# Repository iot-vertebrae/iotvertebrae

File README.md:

# IoT Vertebrae 

The vertebrae bus is an extenxion of the [UEXT](https://www.olimex.com/Products/Modules/UEXT) open bus proposed by Olimex.

This project will be provided as open-source hardware.

## [Using IoT Vertebrae](https://www-binefa-com.translate.goog/index.php/IoT-Vertebrae?_x_tr_sl=ca&_x_tr_tl=en&_x_tr_hl=es&_x_tr_pto=wapp)

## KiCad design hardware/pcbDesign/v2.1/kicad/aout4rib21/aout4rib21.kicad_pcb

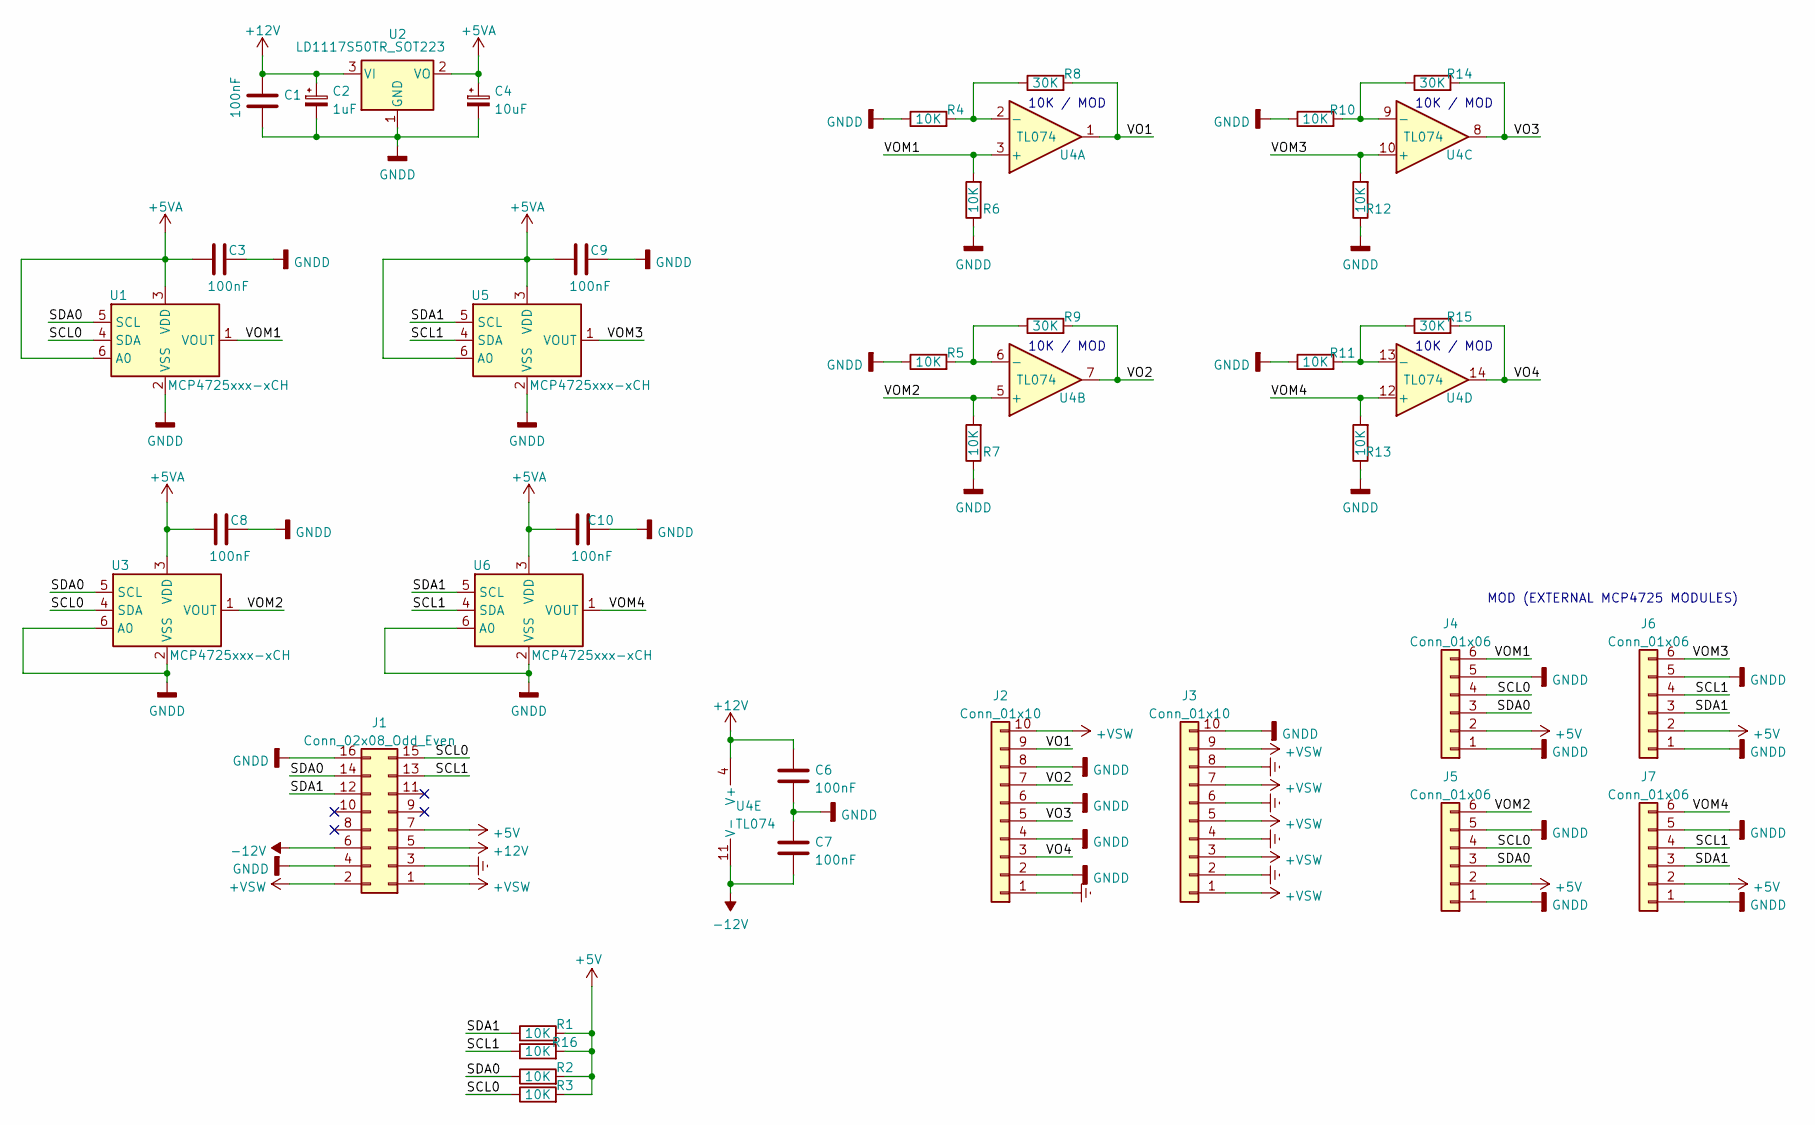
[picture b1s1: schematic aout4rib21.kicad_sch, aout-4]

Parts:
C1, C3, C6, C7, C8, C9, C10: 100nF; C_0805_2012Metric_Pad1.18x1.45mm_HandSolder
C2: 1uF; C_0805_2012Metric_Pad1.18x1.45mm_HandSolder
C4: 10uF; C_0805_2012Metric_Pad1.18x1.45mm_HandSolder
J1: Conn_02x08_Odd_Even; IDC-Header_2x08_P2.54mm_Vertical
J2: Conn_01x10; PhoenixContact_MSTBA_2,5_10-G-5,08_1x10_P5.08mm_Horizontal
J3: Conn_01x10; PhoenixContact_MSTBVA_2,5_10-G-5,08_1x10_P5.08mm_Vertical
J4, J5, J6, J7: Conn_01x06; PinSocket_1x06_P2.54mm_Vertical
R1, R2, R3, R4, R5, R6, R7, R10, R11, R12, R13, R16: 10K; R_0805_2012Metric_Pad1.20x1.40mm_HandSolder
R8, R9, R14, R15: 30K; R_0805_2012Metric_Pad1.20x1.40mm_HandSolder
U1, U3, U5, U6: MCP4725xxx-xCH; SOT-23-6
U2: LD1117S50TR_SOT223; SOT-223-3_TabPin2
U4: TL074; SOIC-14_3.9x8.7mm_P1.27mm

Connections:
+5V: J1.7, J4.2, J5.2, J6.2, J7.2, R1.2, R2.2, R3.2, R16.2
+5VA: C3.1, C4.1, C8.1, C9.1, C10.1, U1.3 (VDD), U1.6 (A0), U2.2 (VO), U3.3 (VDD), U5.3 (VDD), U5.6 (A0), U6.3 (VDD)
+12V: C1.1, C2.1, C6.1, J1.5, U2.3 (VI), U4.4 (V+)
+VSW: J1.1, J1.2, J2.10, J3.1, J3.3, J3.5, J3.7, J3.9
-12V: C7.2, J1.6, U4.11 (V-)
/SCL0: J1.15, J4.4, J5.4, R3.1, U1.4 (SDA), U3.4 (SDA)
/SCL1: J1.13, J6.4, J7.4, R16.1, U5.4 (SDA), U6.4 (SDA)
/SDA0: J1.14, J4.3, J5.3, R2.1, U1.5 (SCL), U3.5 (SCL)
/SDA1: J1.12, J6.3, J7.3, R1.1, U5.5 (SCL), U6.5 (SCL)
/VO1: J2.9, R8.2, U4.1
/VO2: J2.7, R9.2, U4.7
/VO3: J2.5, R14.2, U4.8
/VO4: J2.3, R15.2, U4.14
/VOM1: J4.6, R6.2, U1.1 (VOUT), U4.3 (+)
/VOM2: J5.6, R7.2, U3.1 (VOUT), U4.5 (+)
/VOM3: J6.6, R12.2, U4.10 (+), U5.1 (VOUT)
/VOM4: J7.6, R13.2, U4.12 (+), U6.1 (VOUT)
Earth: J1.3, J2.1, J3.2, J3.4, J3.6, J3.8
GNDD: C1.2, C2.2, C3.2, C4.2, C6.2, C7.1, C8.2, C9.2, C10.2, J1.4, J1.16, J2.2, J2.4, J2.6, J2.8, J3.10, J4.1, J4.5, J5.1, J5.5, J6.1, J6.5, J7.1, J7.5, R4.1, R5.1, R6.1, R7.1, R10.1, R11.1, R12.1, R13.1, U1.2 (VSS), U2.1 (GND), U3.2 (VSS), U3.6 (A0), U5.2 (VSS), U6.2 (VSS), U6.6 (A0)
unnamed: R4.2, R8.1, U4.2 (-)
unnamed: R5.2, R9.1, U4.6 (-)
unnamed: R10.2, R14.1, U4.9 (-)
unnamed: R11.2, R15.1, U4.13 (-)

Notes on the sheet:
10K / MOD
MOD (EXTERNAL MCP4725 MODULES)

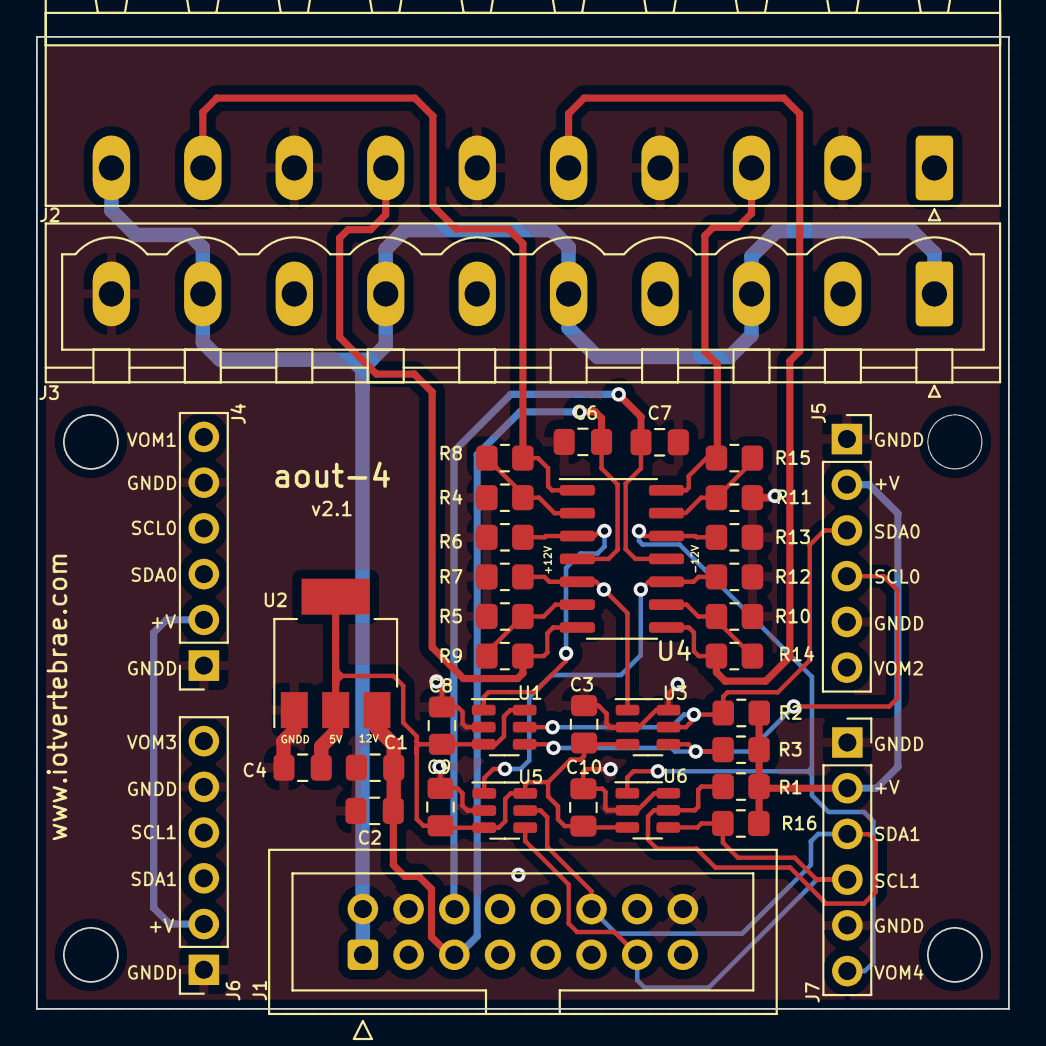
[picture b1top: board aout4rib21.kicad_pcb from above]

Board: 4 copper layers, 54.0 x 54.0 mm, 38 parts (0 on the bottom side), 23 nets.

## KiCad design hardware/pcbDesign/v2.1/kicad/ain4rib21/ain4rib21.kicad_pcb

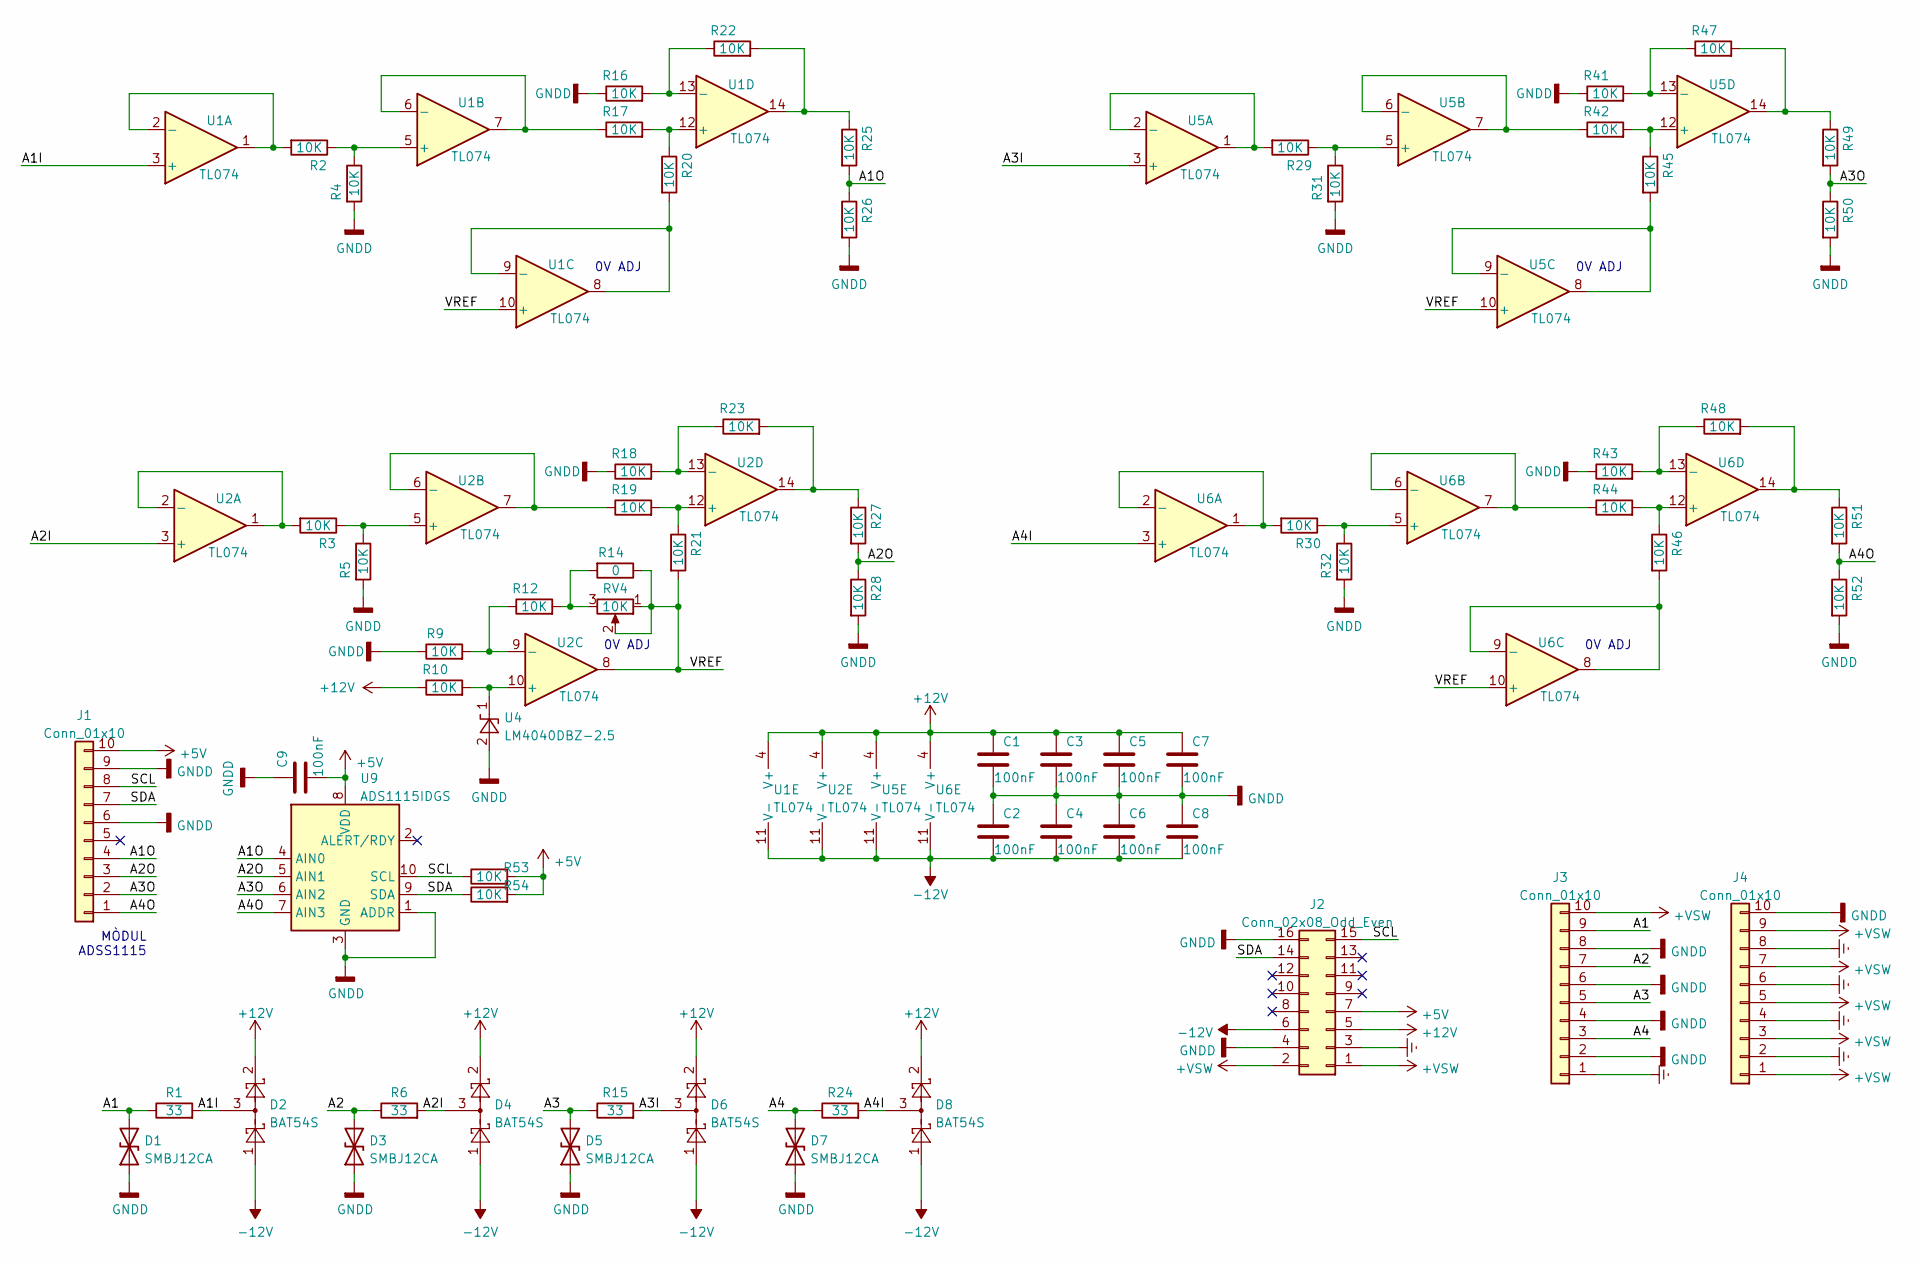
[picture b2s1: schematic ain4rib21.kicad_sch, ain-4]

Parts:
C1, C2, C3, C4, C5, C6, C7, C8, C9: 100nF; C_0805_2012Metric_Pad1.18x1.45mm_HandSolder
D1, D3, D5, D7: SMBJ12CA; D_SMB_Handsoldering
D2, D4, D6, D8: BAT54S; SOT-23
J1: Conn_01x10; PinSocket_1x10_P2.54mm_Vertical
J2: Conn_02x08_Odd_Even; IDC-Header_2x08_P2.54mm_Vertical
J3: Conn_01x10; PhoenixContact_MSTBA_2,5_10-G_1x10_P5.00mm_Horizontal
J4: Conn_01x10; PhoenixContact_MSTBVA_2,5_10-G-5,08_1x10_P5.08mm_Vertical
R1, R6, R15, R24: 33; R_0805_2012Metric_Pad1.20x1.40mm_HandSolder
R2, R3, R4, R5, R9, R10, R12, R16, R17, R18, R19, R20, R21, R22, R23, R25, R26, R27, R28, R29, R30, R31, R32, R41, R42, R43, R44, R45, R46, R47, R48, R49, R50, R51, R52, R53, R54: 10K; R_0805_2012Metric_Pad1.20x1.40mm_HandSolder
R14: 0; R_0805_2012Metric_Pad1.20x1.40mm_HandSolder
RV4: 10K; Potentiometer_Bourns_3296W_Vertical
U1, U2, U5, U6: TL074; SOIC-14_3.9x8.7mm_P1.27mm
U4: LM4040DBZ-2.5; SOT-23
U9: ADS1115IDGS; TSSOP-10_3x3mm_P0.5mm

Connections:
+5V: C9.2, J1.10, J2.7, R53.2, R54.2, U9.8 (VDD)
+12V: C1.1, C3.1, C5.1, C7.1, D2.2, D4.2, D6.2, D8.2, J2.5, R10.1, U1.4 (V+), U2.4 (V+), U5.4 (V+), U6.4 (V+)
+VSW: J2.1, J2.2, J3.10, J4.1, J4.3, J4.5, J4.7, J4.9
-12V: C2.2, C4.2, C6.2, C8.2, D2.1, D4.1, D6.1, D8.1, J2.6, U1.11 (V-), U2.11 (V-), U5.11 (V-), U6.11 (V-)
/A1: D1.2 (A2), J3.9, R1.1
/A1I: D2.3, R1.2, U1.3 (+)
/A1O: J1.4, R25.2, R26.1, U9.4 (AIN0)
/A2: D3.2 (A2), J3.7, R6.1
/A2I: D4.3, R6.2, U2.3 (+)
/A2O: J1.3, R27.2, R28.1, U9.5 (AIN1)
/A3: D5.2 (A2), J3.5, R15.1
/A3I: D6.3, R15.2, U5.3 (+)
/A3O: J1.2, R49.2, R50.1, U9.6 (AIN2)
/A4: D7.2 (A2), J3.3, R24.1
/A4I: D8.3, R24.2, U6.3 (+)
/A4O: J1.1, R51.2, R52.1, U9.7 (AIN3)
/SCL: J1.8, J2.15, R53.1, U9.10 (SCL)
/SDA: J1.7, J2.14, R54.1, U9.9 (SDA)
/VREF: R14.1, R21.2, RV4.1, RV4.2, U1.10 (+), U2.8, U5.10 (+), U6.10 (+)
Earth: J2.3, J3.1, J4.2, J4.4, J4.6, J4.8
GNDD: C1.2, C2.1, C3.2, C4.1, C5.2, C6.1, C7.2, C8.1, C9.1, D1.1 (A1), D3.1 (A1), D5.1 (A1), D7.1 (A1), J1.6, J1.9, J2.4, J2.16, J3.2, J3.4, J3.6, J3.8, J4.10, R4.2, R5.2, R9.1, R16.1, R18.1, R26.2, R28.2, R31.2, R32.2, R41.1, R43.1, R50.2, R52.2, U4.2 (A), U9.1 (ADDR), U9.3 (GND)
unnamed: R2.1, R4.1, U1.5 (+)
unnamed: R2.2, U1.1, U1.2 (-)
unnamed: R3.1, R5.1, U2.5 (+)
unnamed: R3.2, U2.1, U2.2 (-)
unnamed: R10.2, U2.10 (+), U4.1 (K)
unnamed: R9.2, R12.1, U2.9 (-)
unnamed: R12.2, R14.2, RV4.3
unnamed: R16.2, R22.1, U1.13 (-)
unnamed: R17.1, U1.6 (-), U1.7
unnamed: R17.2, R20.1, U1.12 (+)
unnamed: R18.2, R23.1, U2.13 (-)
unnamed: R19.1, U2.6 (-), U2.7
unnamed: R19.2, R21.1, U2.12 (+)
unnamed: R20.2, U1.8, U1.9 (-)
unnamed: R22.2, R25.1, U1.14
unnamed: R23.2, R27.1, U2.14
unnamed: R29.1, R31.1, U5.5 (+)
unnamed: R29.2, U5.1, U5.2 (-)
unnamed: R30.1, R32.1, U6.5 (+)
unnamed: R30.2, U6.1, U6.2 (-)
unnamed: R41.2, R47.1, U5.13 (-)
unnamed: R42.1, U5.6 (-), U5.7
unnamed: R42.2, R45.1, U5.12 (+)
unnamed: R43.2, R48.1, U6.13 (-)
unnamed: R44.1, U6.6 (-), U6.7
unnamed: R44.2, R46.1, U6.12 (+)
unnamed: R45.2, U5.8, U5.9 (-)
unnamed: R46.2, U6.8, U6.9 (-)
unnamed: R47.2, R49.1, U5.14
unnamed: R48.2, R51.1, U6.14

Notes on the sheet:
0V ADJ
MÒDUL ADSS1115

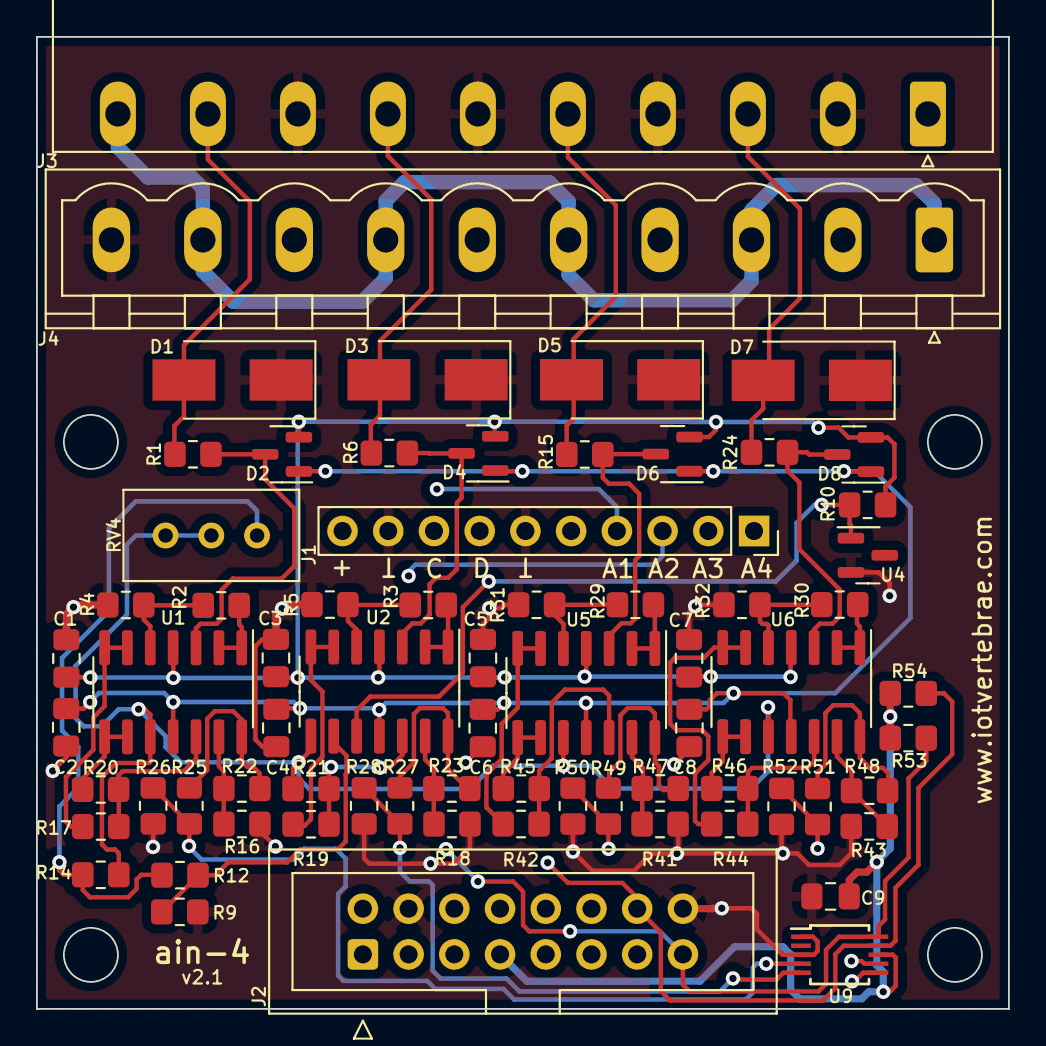
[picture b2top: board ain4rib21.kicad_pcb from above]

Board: 4 copper layers, 54.0 x 54.0 mm, 70 parts (0 on the bottom side), 51 nets.

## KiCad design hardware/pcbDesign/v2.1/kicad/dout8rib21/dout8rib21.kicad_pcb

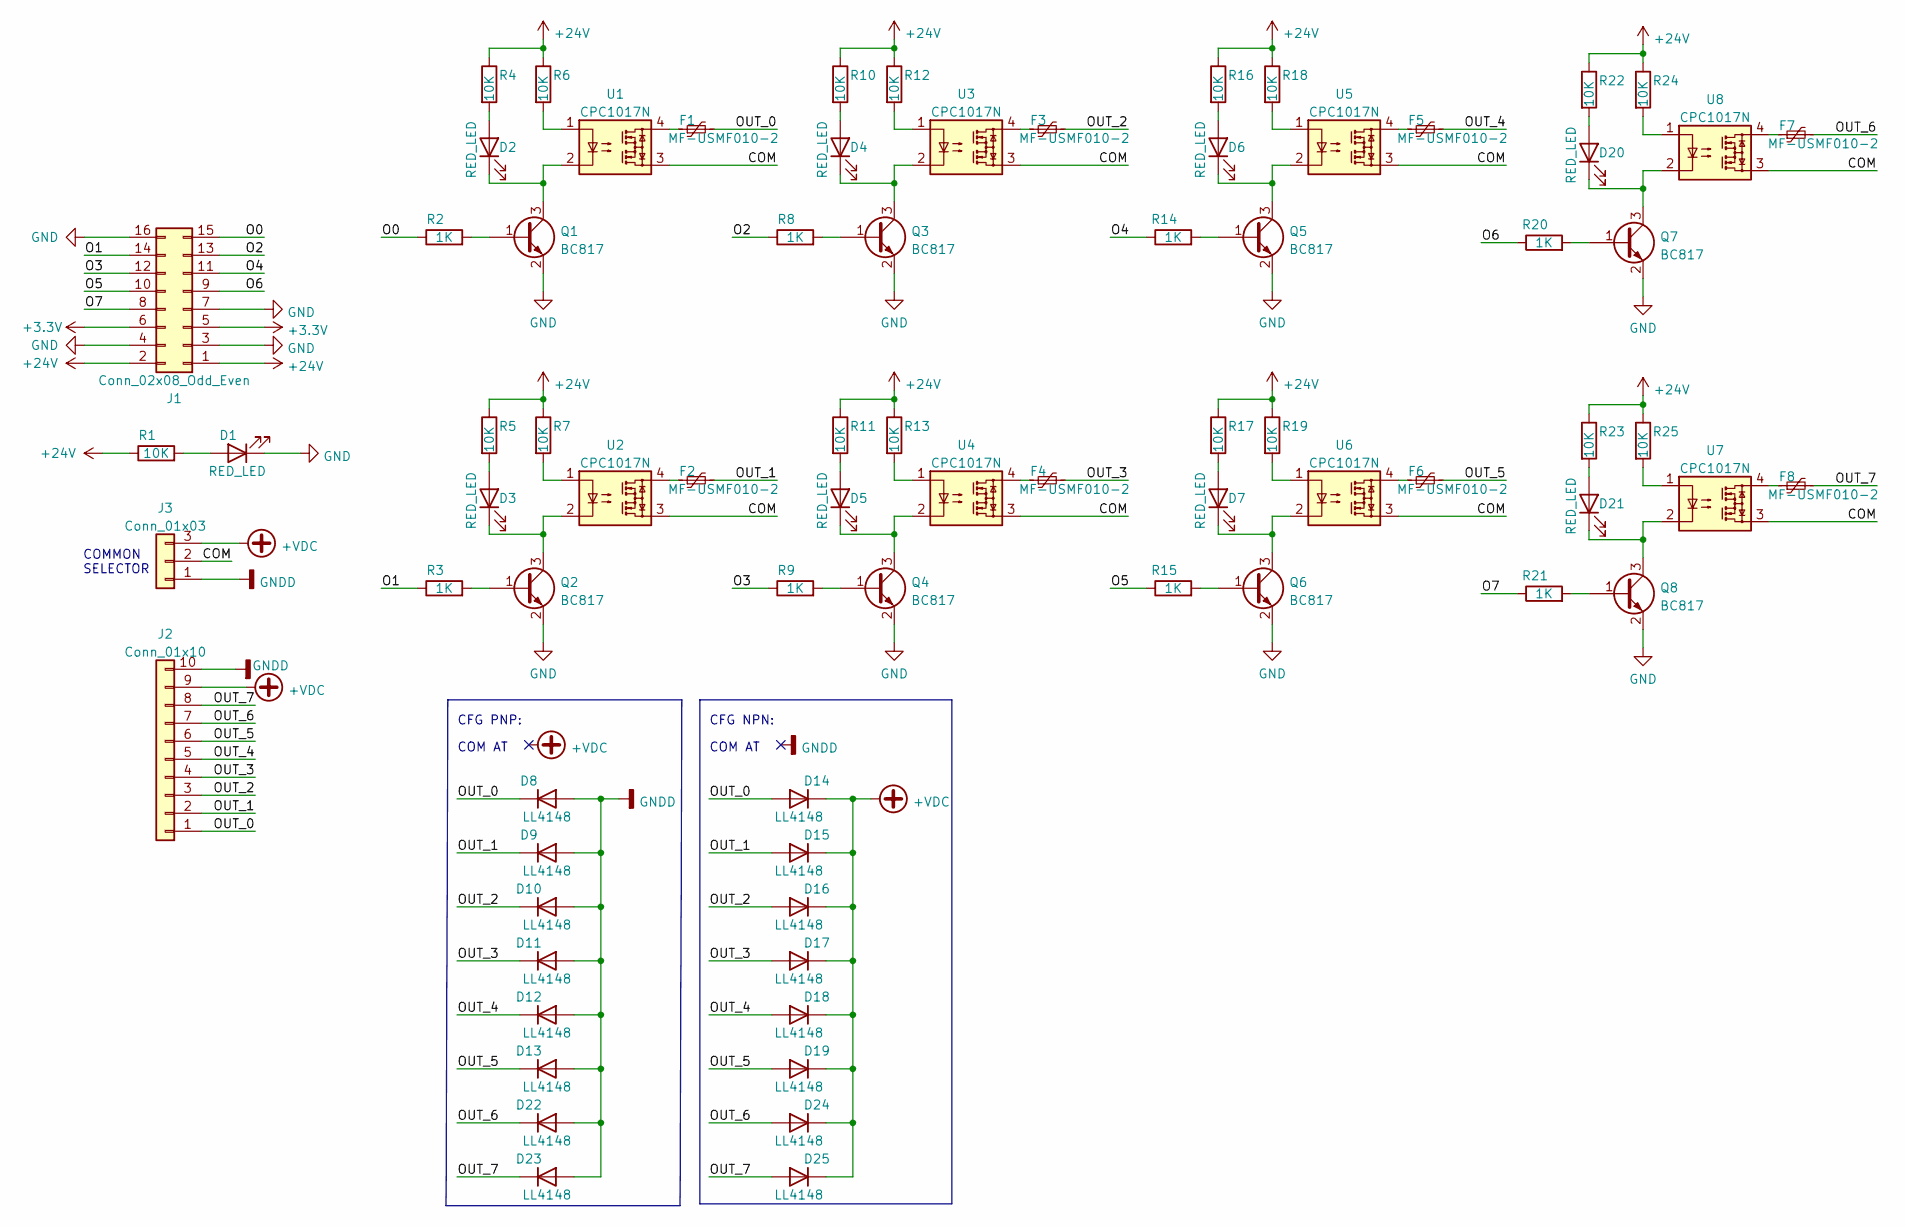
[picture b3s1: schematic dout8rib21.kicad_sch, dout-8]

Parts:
D1, D2, D3, D4, D5, D6, D7, D20, D21: RED_LED; LED_1206_3216Metric_Pad1.42x1.75mm_HandSolder
D8, D9, D10, D11, D12, D13, D14, D15, D16, D17, D18, D19, D22, D23, D24, D25: LL4148; D_MiniMELF
F1, F2, F3, F4, F5, F6, F7, F8: MF-USMF010-2; Fuse_1210_3225Metric_Pad1.42x2.65mm_HandSolder
J1: Conn_02x08_Odd_Even; IDC-Header_2x08_P2.54mm_Vertical
J2: Conn_01x10; PhoenixContact_MSTBA_2,5_10-G-5,08_1x10_P5.08mm_Horizontal
J3: Conn_01x03; PinHeader_1x03_P2.54mm_Vertical
Q1, Q2, Q3, Q4, Q5, Q6, Q7, Q8: BC817; SOT-23
R1, R4, R5, R6, R7, R10, R11, R12, R13, R16, R17, R18, R19, R22, R23, R24, R25: 10K; R_0805_2012Metric_Pad1.20x1.40mm_HandSolder
R2, R3, R8, R9, R14, R15, R20, R21: 1K; R_0805_2012Metric_Pad1.20x1.40mm_HandSolder
U1, U2, U3, U4, U5, U6, U7, U8: CPC1017N; SOP-4_3.8x4.1mm_P2.54mm

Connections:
+3.3V: J1.5, J1.6
+24V: J1.1, J1.2, R1.1, R4.1, R5.1, R6.1, R7.1, R10.1, R11.1, R12.1, R13.1, R16.1, R17.1, R18.1, R19.1, R22.1, R23.1, R24.1, R25.1
+VDC: D14.1 (K), D15.1 (K), D16.1 (K), D17.1 (K), D18.1 (K), D19.1 (K), D24.1 (K), D25.1 (K), J2.9, J3.3
/COM: J3.2, U1.3, U2.3, U3.3, U4.3, U5.3, U6.3, U7.3, U8.3
/O0: J1.15, R2.1
/O1: J1.14, R3.1
/O2: J1.13, R8.1
/O3: J1.12, R9.1
/O4: J1.11, R14.1
/O5: J1.10, R15.1
/O6: J1.9, R20.1
/O7: J1.8, R21.1
/OUT_0: D8.1 (K), D14.2 (A), F1.2, J2.1
/OUT_1: D9.1 (K), D15.2 (A), F2.2, J2.2
/OUT_2: D10.1 (K), D16.2 (A), F3.2, J2.3
/OUT_3: D11.1 (K), D17.2 (A), F4.2, J2.4
/OUT_4: D12.1 (K), D18.2 (A), F5.2, J2.5
/OUT_5: D13.1 (K), D19.2 (A), F6.2, J2.6
/OUT_6: D22.1 (K), D24.2 (A), F7.2, J2.7
/OUT_7: D23.1 (K), D25.2 (A), F8.2, J2.8
GND: D1.1 (K), J1.3, J1.4, J1.7, J1.16, Q1.2 (E), Q2.2 (E), Q3.2 (E), Q4.2 (E), Q5.2 (E), Q6.2 (E), Q7.2 (E), Q8.2 (E)
GNDD: D8.2 (A), D9.2 (A), D10.2 (A), D11.2 (A), D12.2 (A), D13.2 (A), D22.2 (A), D23.2 (A), J2.10, J3.1
unnamed: D1.2 (A), R1.2
unnamed: D2.1 (K), Q1.3 (C), U1.2
unnamed: D2.2 (A), R4.2
unnamed: D3.1 (K), Q2.3 (C), U2.2
unnamed: D3.2 (A), R5.2
unnamed: D4.1 (K), Q3.3 (C), U3.2
unnamed: D4.2 (A), R10.2
unnamed: D5.1 (K), Q4.3 (C), U4.2
unnamed: D5.2 (A), R11.2
unnamed: D6.1 (K), Q5.3 (C), U5.2
unnamed: D6.2 (A), R16.2
unnamed: D7.1 (K), Q6.3 (C), U6.2
unnamed: D7.2 (A), R17.2
unnamed: D20.1 (K), Q7.3 (C), U8.2
unnamed: D20.2 (A), R22.2
unnamed: D21.1 (K), Q8.3 (C), U7.2
unnamed: D21.2 (A), R23.2
unnamed: F1.1, U1.4
unnamed: F2.1, U2.4
unnamed: F3.1, U3.4
unnamed: F4.1, U4.4
unnamed: F5.1, U5.4
unnamed: F6.1, U6.4
unnamed: F7.1, U8.4
unnamed: F8.1, U7.4
unnamed: Q1.1 (B), R2.2
unnamed: Q2.1 (B), R3.2
unnamed: Q3.1 (B), R8.2
unnamed: Q4.1 (B), R9.2
unnamed: Q5.1 (B), R14.2
unnamed: Q6.1 (B), R15.2
unnamed: Q7.1 (B), R20.2
unnamed: Q8.1 (B), R21.2
unnamed: R6.2, U1.1
unnamed: R7.2, U2.1
unnamed: R12.2, U3.1
unnamed: R13.2, U4.1
unnamed: R18.2, U5.1
unnamed: R19.2, U6.1
unnamed: R24.2, U8.1
unnamed: R25.2, U7.1

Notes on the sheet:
COMMON SELECTOR
CFG NPN:
COM AT
CFG PNP:

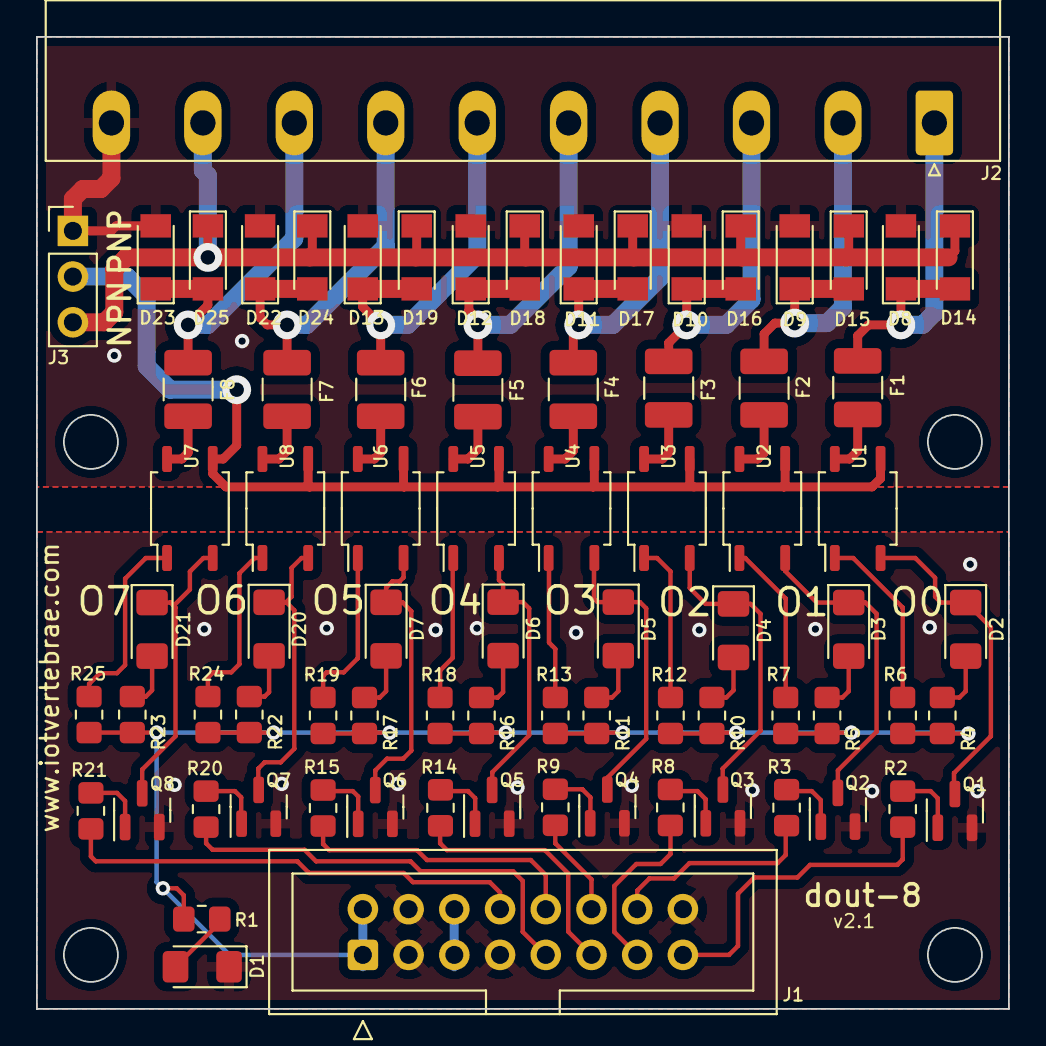
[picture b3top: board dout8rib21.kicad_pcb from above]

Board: 2 copper layers, 54.0 x 54.0 mm, 77 parts (0 on the bottom side), 63 nets.

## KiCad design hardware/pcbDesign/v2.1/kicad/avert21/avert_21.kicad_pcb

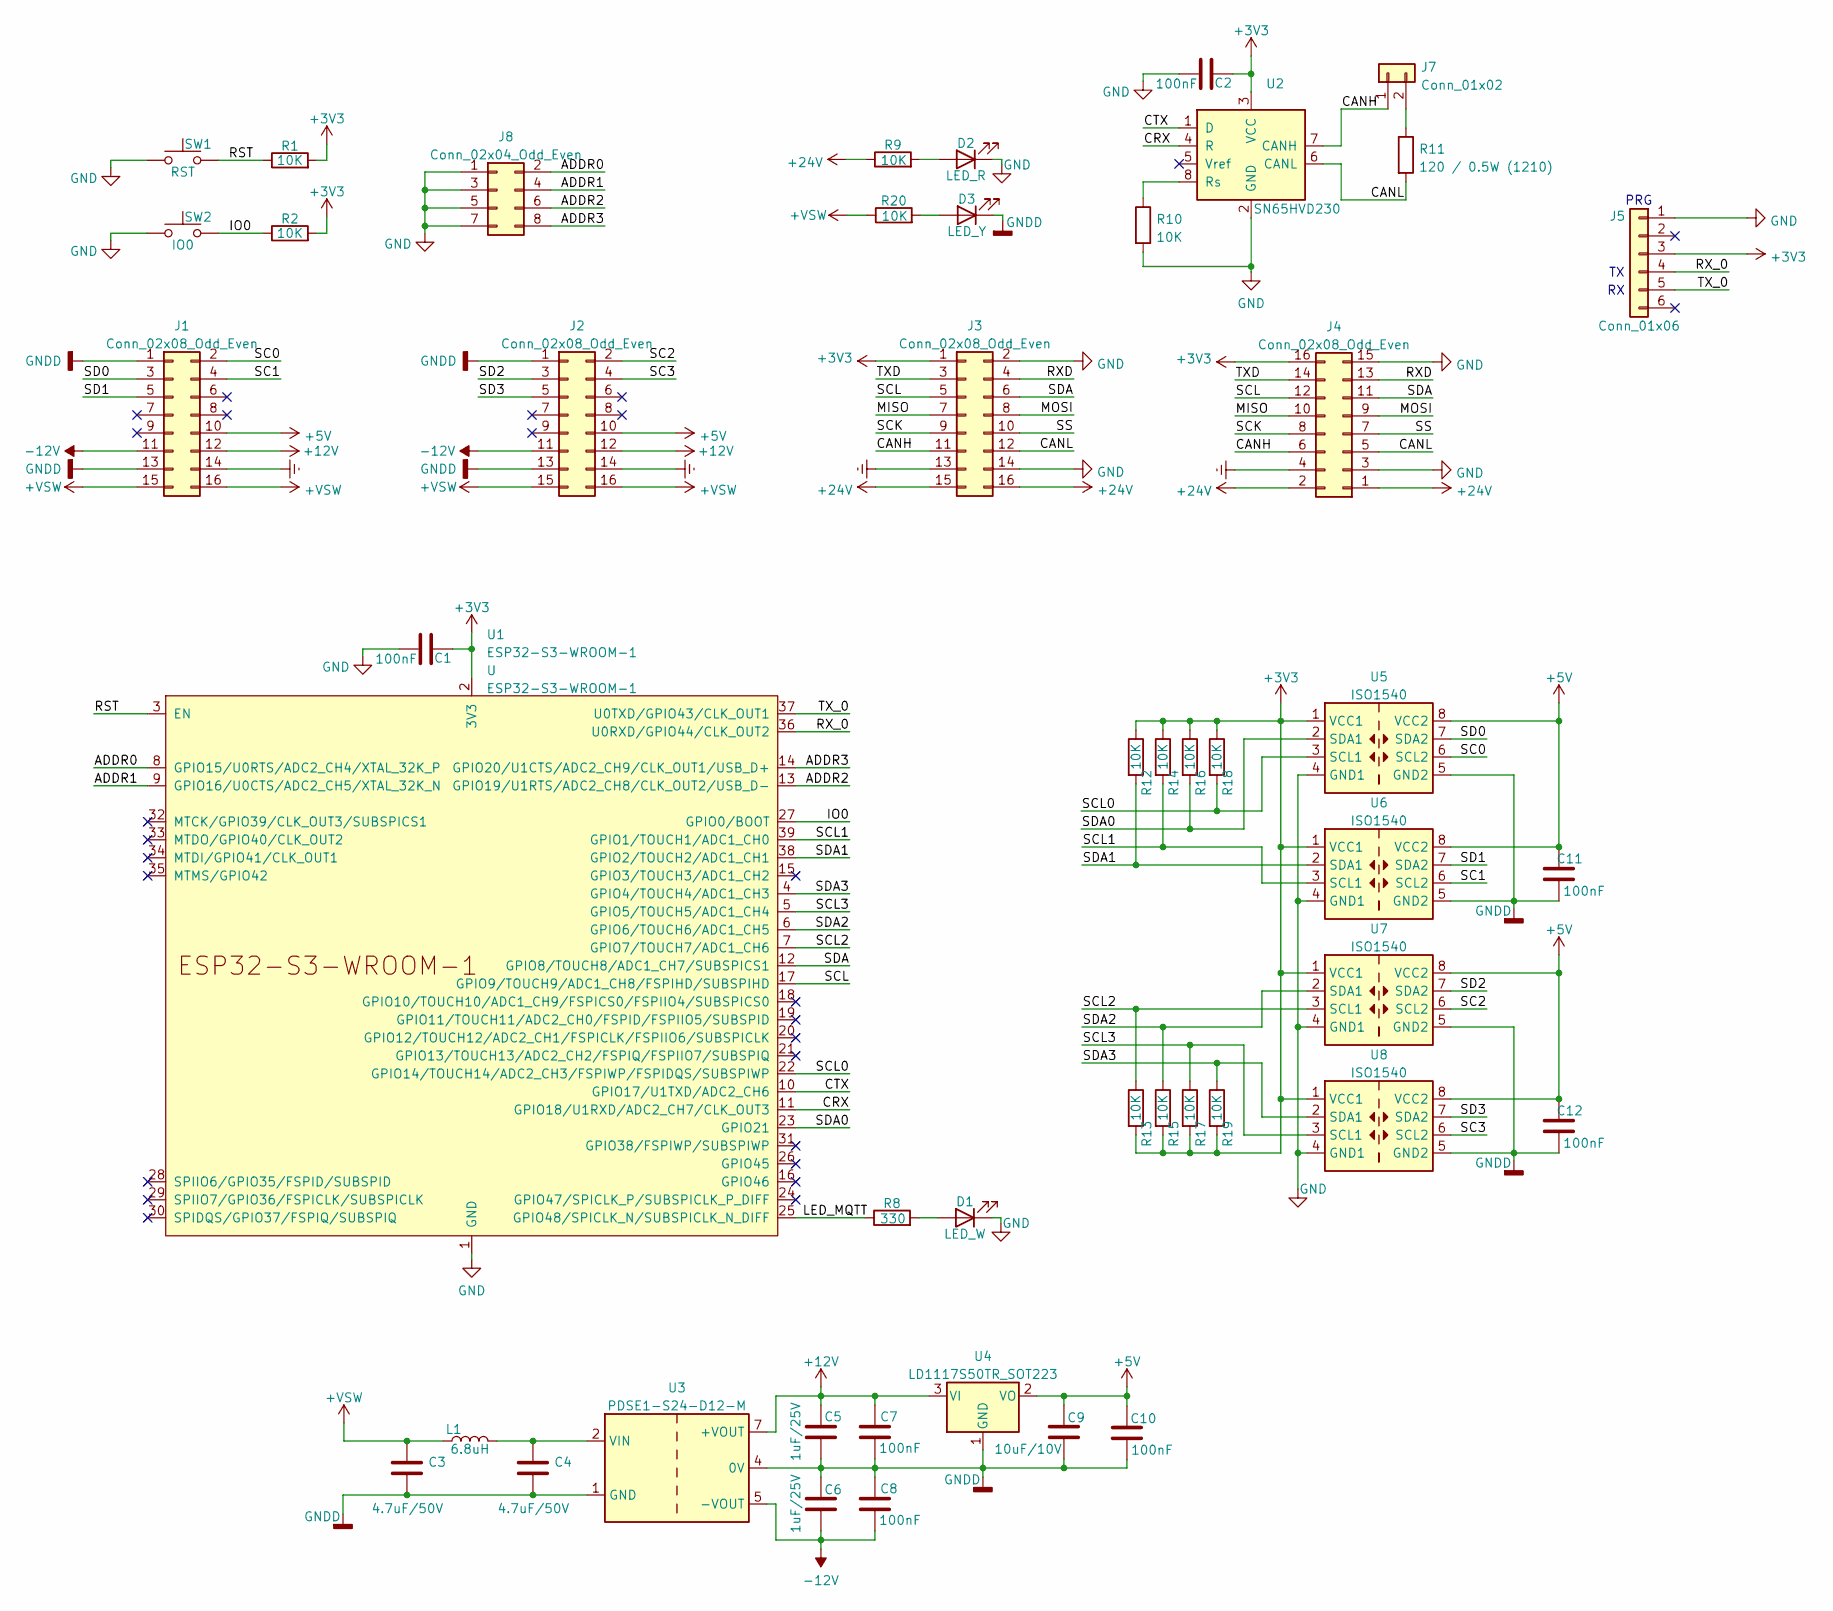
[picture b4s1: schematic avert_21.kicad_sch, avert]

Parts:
C1, C2, C7, C8, C10, C11, C12: 100nF; C_0805_2012Metric_Pad1.18x1.45mm_HandSolder
C3, C4: 4.7uF/50V; C_0805_2012Metric_Pad1.18x1.45mm_HandSolder
C5, C6: 1uF/25V; C_0805_2012Metric_Pad1.18x1.45mm_HandSolder
C9: 10uF/10V; C_0805_2012Metric_Pad1.18x1.45mm_HandSolder
D1: LED_W; LED_1206_3216Metric_Pad1.42x1.75mm_HandSolder
D2: LED_R; LED_1206_3216Metric_Pad1.42x1.75mm_HandSolder
D3: LED_Y; LED_1206_3216Metric_Pad1.42x1.75mm_HandSolder
J1, J2, J3, J4: Conn_02x08_Odd_Even; IDC-Header_2x08_P2.54mm_Vertical
J5: Conn_01x06; PinSocket_1x06_P2.54mm_Vertical
J7: Conn_01x02; PinHeader_1x02_P2.54mm_Vertical
J8: Conn_02x04_Odd_Even; PinHeader_2x04_P2.54mm_Vertical
L1: 6.8uH; L_Bourns_SRP7028A_7.3x6.6mm
R1, R2, R9, R10, R12, R13, R14, R15, R16, R17, R18, R19, R20: 10K; R_0805_2012Metric_Pad1.20x1.40mm_HandSolder
R8: 330; R_0805_2012Metric_Pad1.20x1.40mm_HandSolder
R11: 120 / 0.5W (1210); R_1210_3225Metric_Pad1.30x2.65mm_HandSolder
SW1: RST; SW_SPST_CK_RS282G05A3
SW2: IO0; SW_SPST_CK_RS282G05A3
U1: ESP32-S3-WROOM-1; ESP32-S3-WROOM-1U
U2: SN65HVD230; SOIC-8_3.9x4.9mm_P1.27mm
U3: PDSE1-S24-D12-M; PDESE1-S24-D12-M
U4: LD1117S50TR_SOT223; SOT-223-3_TabPin2
U5, U6, U7, U8: ISO1540; SOIC-8_3.9x4.9mm_P1.27mm

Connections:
+3V3: C1.2, C2.2, J3.1, J4.16, J5.3, R1.2, R2.2, R12.1, R13.2, R14.1, R15.2, R16.1, R17.2, R18.1, R19.2, U1.2 (3V3), U2.3 (VCC), U5.1 (VCC1), U6.1 (VCC1), U7.1 (VCC1), U8.1 (VCC1)
+5V: C9.1, C10.1, C11.2, C12.2, J1.10, J2.10, U4.2 (VO), U5.8 (VCC2), U6.8 (VCC2), U7.8 (VCC2), U8.8 (VCC2)
+12V: C5.1, C7.1, J1.12, J2.12, U3.7 (+VOUT), U4.3 (VI)
+24V: J3.15, J3.16, J4.1, J4.2, R9.1
+VSW: C3.1, J1.15, J1.16, J2.15, J2.16, L1.1, R20.1
-12V: C6.2, C8.2, J1.11, J2.11, U3.5 (-VOUT)
/ADDR0: J8.2, U1.8 (GPIO15/U0RTS/ADC2_CH4/XTAL_32K_P)
/ADDR1: J8.4, U1.9 (GPIO16/U0CTS/ADC2_CH5/XTAL_32K_N)
/ADDR2: J8.6, U1.13 (GPIO19/U1RTS/ADC2_CH8/CLK_OUT2/USB_D-)
/ADDR3: J8.8, U1.14 (GPIO20/U1CTS/ADC2_CH9/CLK_OUT1/USB_D+)
/CANH: J3.11, J4.6, J7.1, U2.7 (CANH)
/CANL: J3.12, J4.5, R11.2, U2.6 (CANL)
/CRX: U1.11 (GPIO18/U1RXD/ADC2_CH7/CLK_OUT3), U2.4 (R)
/CTX: U1.10 (GPIO17/U1TXD/ADC2_CH6), U2.1 (D)
/IO0: R2.1, SW2.2, U1.27 (GPIO0/BOOT)
/LED_MQTT: R8.1, U1.25 (GPIO48/SPICLK_N/SUBSPICLK_N_DIFF)
/MISO: J3.7, J4.10
/MOSI: J3.8, J4.9
/RST: R1.1, SW1.2, U1.3 (EN)
/RXD: J3.4, J4.13
/RX_0: J5.4, U1.36 (U0RXD/GPIO44/CLK_OUT2)
/SC0: J1.2, U5.6 (SCL2)
/SC1: J1.4, U6.6 (SCL2)
/SC2: J2.2, U7.6 (SCL2)
/SC3: J2.4, U8.6 (SCL2)
/SCK: J3.9, J4.8
/SCL: J3.5, J4.12, U1.17 (GPIO9/TOUCH9/ADC1_CH8/FSPIHD/SUBSPIHD)
/SCL0: R18.2, U1.22 (GPIO14/TOUCH14/ADC2_CH3/FSPIWP/FSPIDQS/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), U5.3 (SCL1)
/SCL1: R14.2, U1.39 (GPIO1/TOUCH1/ADC1_CH0), U6.3 (SCL1)
/SCL2: R13.1, U1.7 (GPIO7/TOUCH7/ADC1_CH6), U7.3 (SCL1)
/SCL3: R17.1, U1.5 (GPIO5/TOUCH5/ADC1_CH4), U8.3 (SCL1)
/SD0: J1.3, U5.7 (SDA2)
/SD1: J1.5, U6.7 (SDA2)
/SD2: J2.3, U7.7 (SDA2)
/SD3: J2.5, U8.7 (SDA2)
/SDA: J3.6, J4.11, U1.12 (GPIO8/TOUCH8/ADC1_CH7/SUBSPICS1)
/SDA0: R16.2, U1.23 (GPIO21), U5.2 (SDA1)
/SDA1: R12.2, U1.38 (GPIO2/TOUCH2/ADC1_CH1), U6.2 (SDA1)
/SDA2: R15.1, U1.6 (GPIO6/TOUCH6/ADC1_CH5), U7.2 (SDA1)
/SDA3: R19.1, U1.4 (GPIO4/TOUCH4/ADC1_CH3), U8.2 (SDA1)
/SS: J3.10, J4.7
/TXD: J3.3, J4.14
/TX_0: J5.5, U1.37 (U0TXD/GPIO43/CLK_OUT1)
Earth: J1.14, J2.14, J3.13, J4.4
GND: C1.1, C2.1, D1.1 (K), D2.1 (K), J3.2, J3.14, J4.3, J4.15, J5.1, J8.1, J8.3, J8.5, J8.7, R10.2, SW1.1, SW2.1, U1.1 (GND), U1.40 (GND), U1.41 (GND), U2.2 (GND), U5.4 (GND1), U6.4 (GND1), U7.4 (GND1), U8.4 (GND1)
GNDD: C3.2, C4.2, C5.2, C6.1, C7.2, C8.1, C9.2, C10.2, C11.1, C12.1, D3.1 (K), J1.1, J1.13, J2.1, J2.13, U3.1 (GND), U3.4 (0V), U4.1 (GND), U5.5 (GND2), U6.5 (GND2), U7.5 (GND2), U8.5 (GND2)
unnamed: C4.1, L1.2, U3.2 (VIN)
unnamed: D1.2 (A), R8.2
unnamed: D2.2 (A), R9.2
unnamed: D3.2 (A), R20.2
unnamed: J7.2, R11.1
unnamed: R10.1, U2.8 (Rs)

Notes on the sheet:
PRG

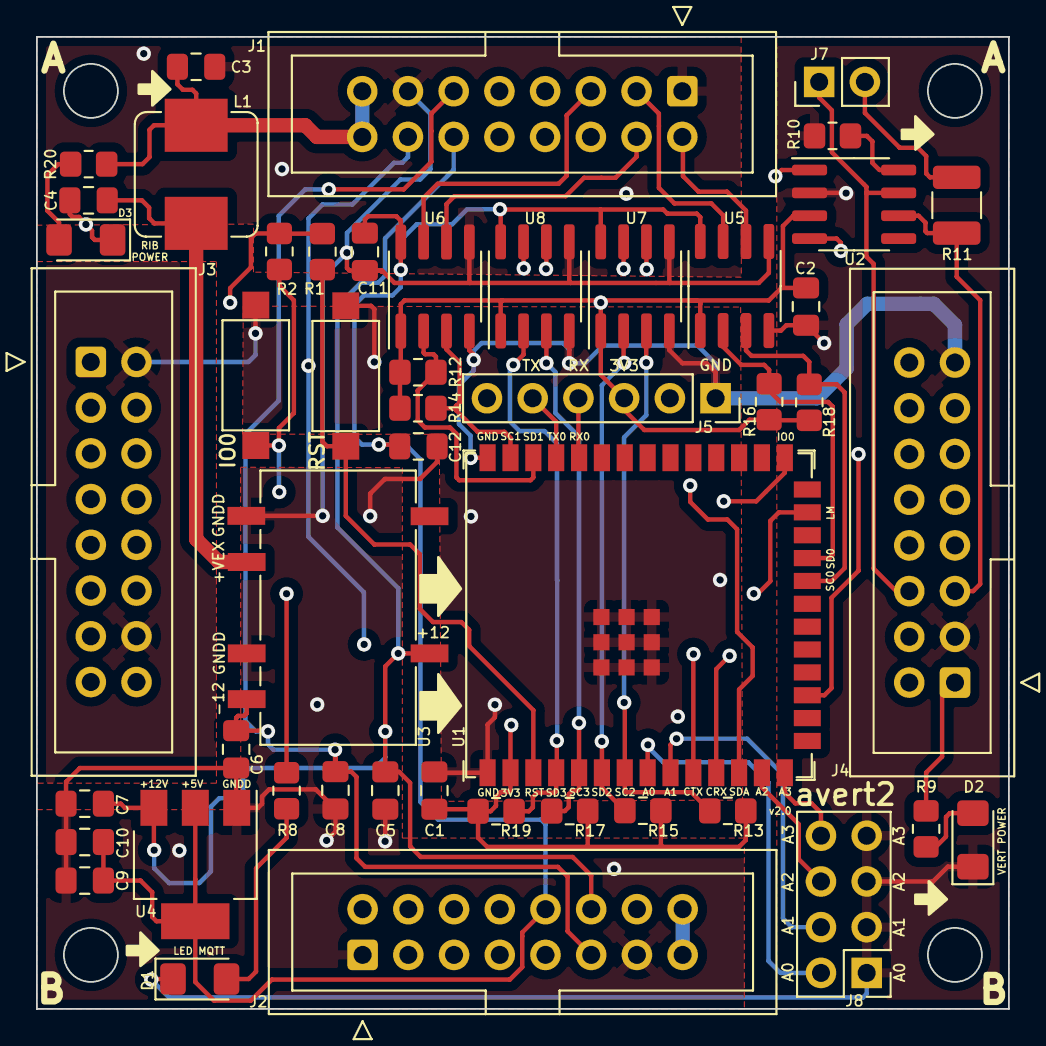
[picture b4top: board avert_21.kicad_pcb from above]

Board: 4 copper layers, 54.0 x 54.0 mm, 48 parts (0 on the bottom side), 52 nets.
